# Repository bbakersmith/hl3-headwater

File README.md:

# HL3 Headwater

A digital clock source built around an ATMega328P for driving eurorack audio and
video synthesizer modules. Features include syncronization with external CV and
MIDI clock sources, three separate CV output channels, MIDI clock output, two
discreet multipliers, saving and loading of custom presets, LCD and rotary
encoder based UI, and an SPI API for serial control.

# License

Copyright Ben Baker-Smith 2019.

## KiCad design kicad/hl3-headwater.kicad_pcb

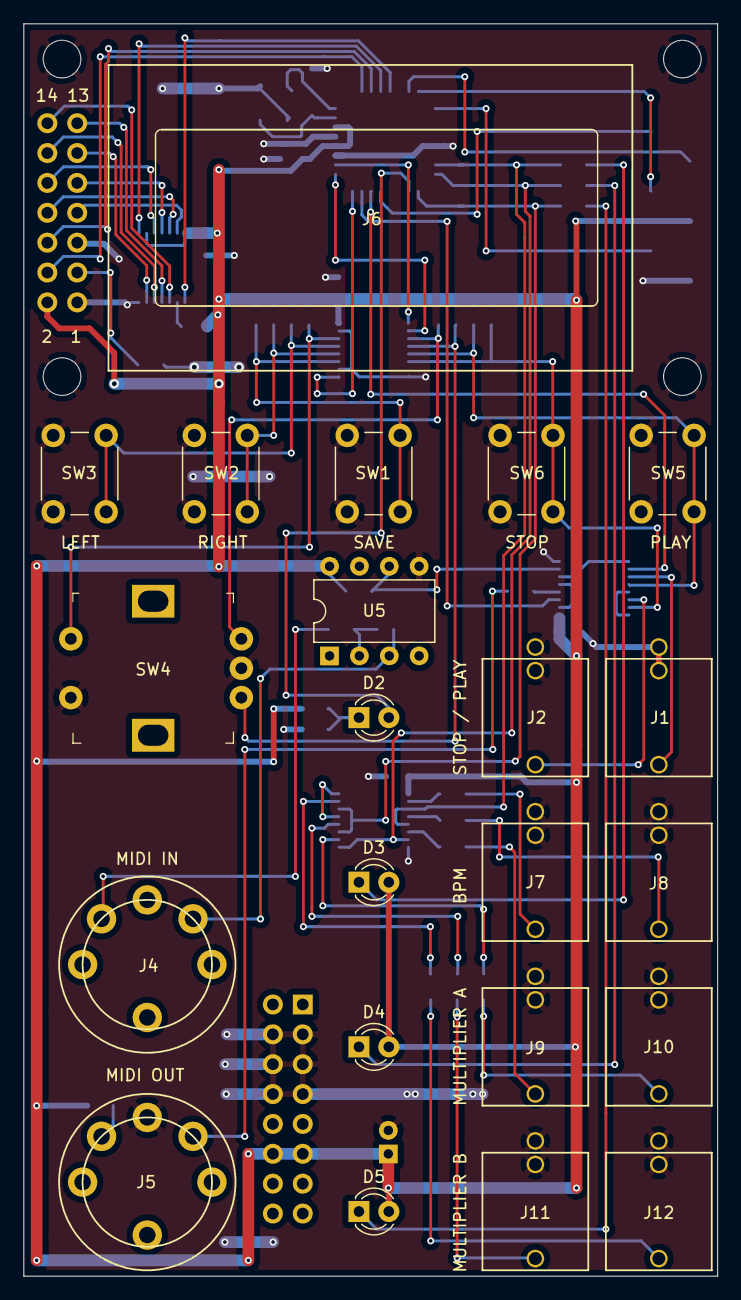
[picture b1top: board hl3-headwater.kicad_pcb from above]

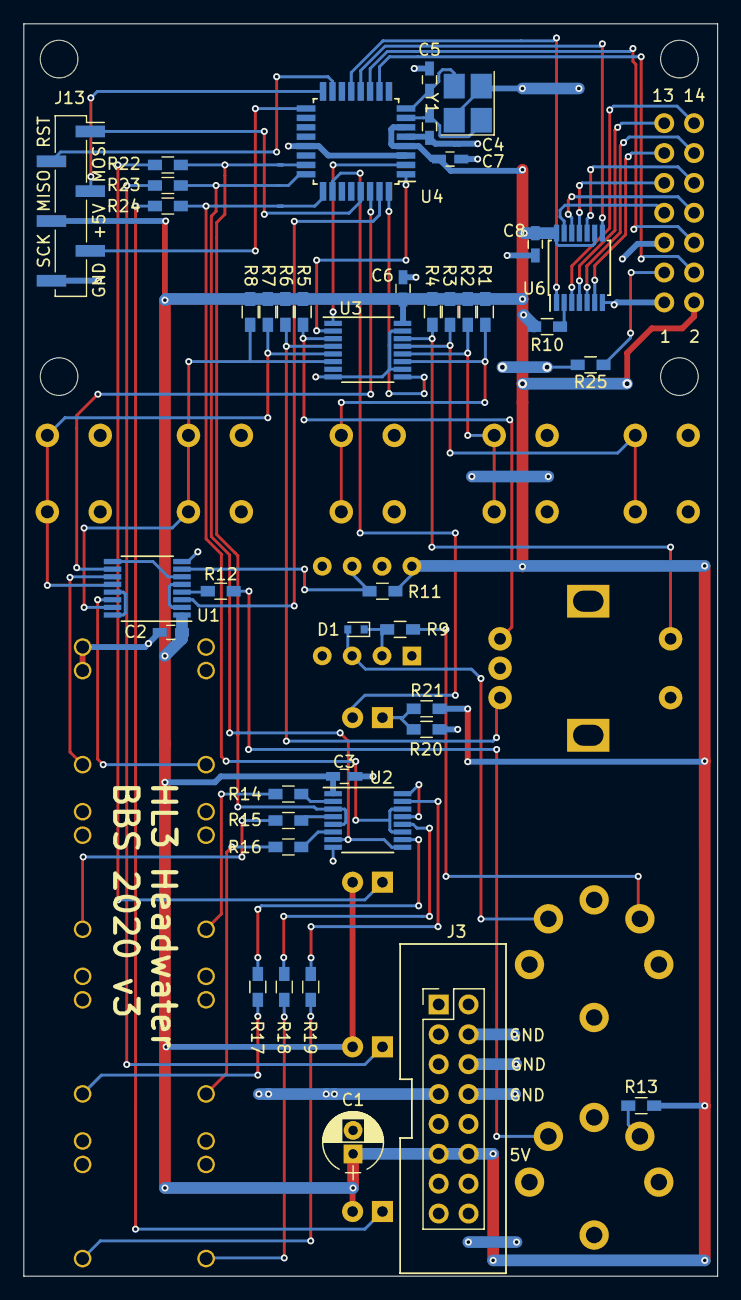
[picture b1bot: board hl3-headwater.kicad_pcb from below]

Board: 2 copper layers, 59.0 x 106.5 mm, 64 parts (42 on the bottom side), 66 nets.

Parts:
C1: 10uF; CP_Radial_D5.0mm_P2.00mm
C2, C3, C6, C7, C8: 100nF; C_0603_HandSoldering
C4, C5: 20pF; C_0603_HandSoldering
D1: D; D_SOD-523
D2: Stop / Play; LED_D3.0mm
D3, D4, D5: LED; LED_D3.0mm
J1: Play; Synthrotek_mono_audio_jack_with_switch
J2: Stop; Synthrotek_mono_audio_jack_with_switch
J3: Eurorack Power; Eurorack_Power_16pin
J4, J5: DIN-5_180degree; SD-50BV-5DIN
J6: LCD Header; LCD_0802A
J7: BPM1; Synthrotek_mono_audio_jack_with_switch
J8: BPM2; Synthrotek_mono_audio_jack_with_switch
J9: Multiplier A1; Synthrotek_mono_audio_jack_with_switch
J10: Multiplier A2; Synthrotek_mono_audio_jack_with_switch
J11: Multiplier B1; Synthrotek_mono_audio_jack_with_switch
J12: Multiplier B2; Synthrotek_mono_audio_jack_with_switch
J13: Conn_01x06_Female; Pin_Header_Straight_1x06_Pitch2.54mm_SMD_Pin1Right
R1, R2, R3, R4, R5, R6, R7, R8, R10, R11, R20, R21, R22, R23, R24: 10K; R_0603_HandSoldering
R9, R12, R13: 220; R_0603_HandSoldering
R14, R15, R16, R17, R18, R19: 1K; R_0603_HandSoldering
R25: 2K2; R_0603_HandSoldering
SW1: Save; SW_PUSH_6mm_h8mm
SW2: Right; SW_PUSH_6mm_h8mm
SW3: Left; SW_PUSH_6mm_h8mm
SW4: Rotary Encoder; Rotary_Encoder_Switched_PEC11R
SW5: Play; SW_PUSH_6mm_h8mm
SW6: Stop; SW_PUSH_6mm_h8mm
U1: 4049; TSSOP-16_4.4x5mm_Pitch0.65mm
U2: 4049 Outputs; TSSOP-16_4.4x5mm_Pitch0.65mm
U3: 74165 UI Shift Register; TSSOP-16_4.4x5mm_Pitch0.65mm
U4: ATmega328P-AU; TQFP-32_7x7mm_Pitch0.8mm
U5: 6N137; DIP-8_W7.62mm
U6: 74164 LCD Shift Register; TSSOP-14_4.4x5mm_Pitch0.65mm
Y1: 16MHz Crystal; Crystal_SMD_3225-4pin_3.2x2.5mm_HandSoldering

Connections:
+5V: C1.1, C2.1, C3.1, C6.1, C7.1, C8.2, D3.2, D4.2, D5.2, J3.11, J3.12, J6.2, J13.4, R1.2, R2.2, R3.2, R4.2, R5.2, R6.2, R7.2, R8.2, R10.1, R11.1, R13.1, R20.1, U1.1, U2.1, U3.16, U4.4, U4.6, U5.8, U6.9, U6.14
/BPM_OUT: R22.1, U2.3, U2.5, U4.23
/INPUT_LEFT: R3.1, SW3.2, U3.13
/INPUT_PLAY: R7.1, SW5.2, U1.12, U3.5
/INPUT_RE_A: R6.1, SW4.A, U3.4
/INPUT_RE_B: R5.1, SW4.B, U3.3
/INPUT_RE_SW: R4.1, SW4.S2, U3.14
/INPUT_RIGHT: R2.1, SW2.2, U3.12
/INPUT_SAVE: R1.1, SW1.2, U3.11
/INPUT_STOP: R8.1, SW6.2, U1.15, U3.6
/LCD_0: J6.7, U6.13
/LCD_1: J6.8, U6.12
/LCD_2: J6.9, U6.11
/LCD_3: J6.10, U6.10
/LCD_4: J6.11, U6.6
/LCD_5: J6.12, U6.5
/LCD_6: J6.13, U6.4
/LCD_7: J6.14, U6.3
/LCD_E: J6.6, U4.11
/LCD_RS: J6.4, U4.10
/LCD_SR_CLK: U4.12, U6.8
/LCD_SR_DATA: U4.13, U6.1
/MIDI_IN: U1.10, U4.30
/MIDI_OUT: U1.3, U4.31
/MULTIPLIER_A_OUT: R23.1, U2.7, U2.9, U4.24
/MULTIPLIER_B_OUT: R24.1, U2.11, U2.14, U4.25
/RESET: J13.1, U4.29
/SPI_MISO: J13.3, U4.16
/SPI_MOSI: J13.2, U4.15
/SPI_SCK: J13.5, U4.17
/STOP_PLAY_OUT: D2.2, U4.26
/UI_CLK: U3.2, U4.1
/UI_INPUT: U3.9, U4.32
/UI_SHIFT: U3.1, U4.2
/XTAL1: C4.1, U4.7, Y1.1
/XTAL2: C5.1, U4.8, Y1.3
GND: C1.2, C2.2, C3.2, C4.2, C5.2, C6.2, C7.2, C8.1, J1.2, J1.3, J2.2, J2.3, J3.3, J3.4, J3.5, J3.6, J3.7, J3.8, J5.2, J6.1, J6.5, J7.2, J7.3, J8.2, J8.3, J9.2, J9.3, J10.2, J10.3, J11.2, J11.3, J12.2, J12.3, J13.6, R21.2, R25.2, SW1.1, SW2.1, SW3.1, SW4.C, SW4.S1, SW5.1, SW6.1, U1.8, U2.8, U3.8, U3.10, U3.15, U4.3, U4.5, U4.21, U5.5, U6.7, Y1.2, Y1.4
unnamed: D1.1, R9.1, U5.2
unnamed: D1.2, J4.5, U5.3
unnamed: D2.1, R20.2, R21.1
unnamed: D3.1, R22.2
unnamed: D4.1, R23.2
unnamed: D5.1, R24.2
unnamed: J1.1, U1.11
unnamed: J2.1, U1.14
unnamed: J4.4, R9.2
unnamed: J5.4, R13.2
unnamed: J5.5, R12.2
unnamed: J6.3, R25.1
unnamed: J7.1, R14.1
unnamed: J8.1, R15.1
unnamed: J9.1, R16.1
unnamed: J10.1, R17.1
unnamed: J11.1, R18.1
unnamed: J12.1, R19.1
unnamed: R10.2, U6.2
unnamed: R11.2, U1.7, U5.6
unnamed: R12.1, U1.4
unnamed: R14.2, U2.2
unnamed: R15.2, U2.4
unnamed: R16.2, U2.6
unnamed: R17.2, U2.10
unnamed: R18.2, U2.12
unnamed: R19.2, U2.15
unnamed: U1.2, U1.5
unnamed: U1.6, U1.9

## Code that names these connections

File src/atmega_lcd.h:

/**
 * @file atmega_lcd.h
 *
 * GPIO setup and write functions for updating 16x02 style LCD display.
 */

#ifndef _ATMEGA_LCD_H_
#define _ATMEGA_LCD_H_

#define F_CPU 16000000UL  // 16 MHz

#include "stdbool.h"
#include "stdint.h"
#include <avr/io.h>
#include <util/delay.h>

#define LCD_PORT PORTD
#define LCD_DDR DDRD

#define LCD_RS_PIN PORTD6
#define LCD_E_PIN PORTD7

#define LCD_SR_PORT PORTB
#define LCD_SR_DDR DDRB

#define LCD_SR_CLK_PIN PORTB0
#define LCD_SR_DATA_PIN PORTB1

/**
 * Initialize GPIO for outputs to LCD.
 */
void atmega_lcd_init(void);

/**
 * Send data to LCD.
 *
 * @param State of RS pin
 * @param Data byte
 */
void atmega_lcd_send(bool rs, uint8_t data);

/**
 * Send command to LCD.
 *
 * @param Command byte
 */
void atmega_lcd_send_cmd(uint8_t data);

/**
 * Send data to LCD.
 *
 * @param Data byte
 */
void atmega_lcd_send_data(uint8_t data);

#endif

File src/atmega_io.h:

/**
 * @file atmega_io.h
 *
 * Headwater GPIO setup and read / write functions for the Atmega328p.
 */

#ifndef _ATMEGA_IO_H_
#define _ATMEGA_IO_H_

#include "stdbool.h"
#include "stdint.h"
#include <avr/io.h>

#include "bytes.h"

#define UI_PIN PIND
#define UI_PORT PORTD
#define UI_DDR DDRD

#define UI_INPUT_PIN PORTD2
#define UI_CLK_PIN PORTD3
#define UI_SHIFT_PIN PORTD4

#define OUTPUT_PORT PORTC
#define OUTPUT_DDR DDRC

#define BPM_PIN PORTC0
#define MULTIPLIER_A_PIN PORTC1
#define MULTIPLIER_B_PIN PORTC2
#define STOP_PLAY_PIN PORTC4

/**
 * Set state of BPM output pin.
 */
void atmega_io_bpm_output(bool enabled);

/**
 * Set state of multiplier A output pin.
 */
void atmega_io_multiplier_a_output(bool enabled);

/**
 * Set state of multiplier A output pin.
 */
void atmega_io_multiplier_b_output(bool enabled);

/**
 * Set state of stop / play LED indicator pin.
 */
void atmega_io_stop_play_output(bool enabled);

/**
 * Read inputs from parallel to serial shift register.
 *
 * @param Number of inputs to sample, max 8
 *
 * @return Byte with each bit representing the state of an input
 */
uint8_t atmega_io_sample_inputs(uint8_t count);

/**
 * Initialize GPIO for outputs and parallel to serial shift register.
 */
void atmega_io_init(void);

#endif

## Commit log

2018-10-20 Initial
2018-10-22 Holy tested headwater module, batman
2018-10-22 Stop, start, other counter functionality
2018-10-22 Functional style to outputs
2018-10-23 atmega build
2018-10-25 Crazy lookup approach works
2018-12-04 MAX7221 and 32bit division functioning
2018-12-05 Rotary count up and down and switch to reset
2018-12-05 Speed up SPI to 1mhz
2018-12-05 BPM counter working!
2018-12-05 Change incrementation amount with encoder switch
2018-12-18 Multiplexing, too slow
2018-12-18 SPI slave working with bus pirate
2018-12-22 Separate clock from ui mcu
2018-12-22 Outputs pull down for inverting hex buffer
2019-01-05 API rewrite
2019-01-05 API new payload and handle request
2019-01-06 API interrupt handler
2019-01-06 First get API commands
2019-01-09 API functions
2019-01-09 Lots of cleanup
2019-01-09 Minor cleanup
2019-01-12 Massive renaming and conversion to embedded structs without pointers, also API integration with mcu
2019-01-13 API and change flag integrated into atmega
2019-01-13 Volatile everywhere, moving toward generic channels with mult mod
2019-01-19 OMG HUGE STUPID WIP COMMIT
2019-01-28 LCD refresh working with minimal compiler optimizations
2019-01-28 Practical experiments in LCD control
2019-02-16 Headwater LCD first screen framed out
2019-02-16 Parallel to serial ui inputs 74165
2019-02-24 Debounce, ui
2019-02-24 Debounce integrated into atmega
2019-02-24 Satisfy compiler, start integrating ui
2019-02-24 Cursor movement, more integration work in progress
2019-03-11 Headwater UI handling display and state
2019-03-11 Added multiplier a to ui
2019-03-12 Compile with optimizations
2019-03-12 Multiplier B and character 0 blanking bugfix
2019-03-13 Modify with restrictions and button hold counts
2019-03-16 Ugly, but preset load / save working
2019-03-17 Add Mode field to UI
2019-03-17 Move headwater_lcd into headwater_ui
2019-03-17 Multiplier B online
2019-03-17 Refactor main into setup functions for sanity
2019-03-17 Renaming
2019-03-18 lcd_handle_interrupt
2019-03-18 Preserve eeprom on flash
2019-03-18 Consolidate lcd initialization
2019-03-18 Move preset handling to headwater_ui
2019-03-18 Fix tests for lcd_handle_interrupt, still failing
2019-03-18 Fix LCD update always firing, only fire on change
2019-03-23 compiler options
2019-03-23 don't load presets if preset id doesn't match
2019-03-23 update display when change is committed
2019-03-23 don't commit preset change if loading fails
2019-03-23 HeadwaterInputs
2019-03-23 headwater_ui_inputs out of atmega_headwater
2019-03-23 Separate headwater_state from api
2019-03-23 headwater_ui_handle_inputs
2019-03-23 commit change immediately if encoder sw pressed
2019-03-24 move libs to lib, remove old, fix tests
2019-03-24 atmega_headwater moved to atmega_io and main
2019-03-24 loc make target
2019-03-24 first pass at external mode
2019-03-25 WIP external mode
2019-03-26 more WIP junk
2019-03-26 samples_per_second must be 32 bit
2019-03-26 ext working, handful of known bugs
2019-04-03 fix bug: playback stopping at samples_since_reset_count overflow
2019-04-03 bpm uint16 everywhere
2019-04-10 even distribution algorithm prototyped in sort.py
2019-04-10 comments
2019-04-24 Integrate even distribution into main cycle fn
2019-04-24 Allow multiplier of 0
2019-04-24 TODO
2019-04-26 WIP but MIDI out working to MPC
2019-05-04 Dummy midi writer
2019-05-04 QueueFifo255
2019-05-07 async MIDI write integrated into main
2019-05-12 Doxygen docs and stdbool
2019-05-13 Compiler flags
2019-05-13 enum naming to camelcase per convention
2019-05-14 rename api_new_request > api_request_new
2019-05-15 Resolve outstanding TODO comments
2019-05-15 only update channel samples per beat after a beat
2019-05-15 MIDI continue if already playing when play hits
2019-05-15 docs and variable naming
2019-05-15 DummyStruct
2019-05-15 brief descriptions of all library headers
2019-05-15 display test LOC separately
2019-05-15 PHONY
2019-05-17 move MIDI fully into headwater state
2019-05-17 WIP midi mode reads, not functional
2019-05-24 kicad
2019-05-24 tap mode WIP
2019-05-26 build dir
2019-05-26 overridable test compiler
2019-05-29 schematic io
2019-06-12 decoupling caps, change schematic symbol for jacks
2019-07-07 MIDI schematic
2019-07-10 Schematic updates
2019-10-21 README
2020-01-22 stop / play LED output
2020-02-11 v3 ordered
2020-02-24 Reverse rotary encoder direction
